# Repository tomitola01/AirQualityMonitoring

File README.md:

# Air Quality Monitoring System
This repository includes the Arduino C code (monitoring_arduinoC.ino) for the air quality monitoring system. To be used with the ESP32 microcontroller, a BME680 sensor, a push button for input, and an Adafruit 128x32 OLED. <br />
\
<br/>
\
Below shows the Adafruit display on the breadboard prototype with the system working as expected.
<br/>
\
The circuit schematics and PCB for the system can be found in the circuit_files folder. <br />
The CAD folder contains the 3D design of the monitoring system housing. Fusion 360 is needed to open the .fz3 file. <br />
\
Also included is the HTML file (monitoring_webserver.html) to build the web server with the ESP32. <br />
To build the server: 
1. Download the Monitoring_Code folder
2. Open the project using Ardunio
3. Upload the sketch to the ESP32 and run it
4. Open the serial monitor and use obtain the ESP32's IP address
5. Enter IP address into web browser

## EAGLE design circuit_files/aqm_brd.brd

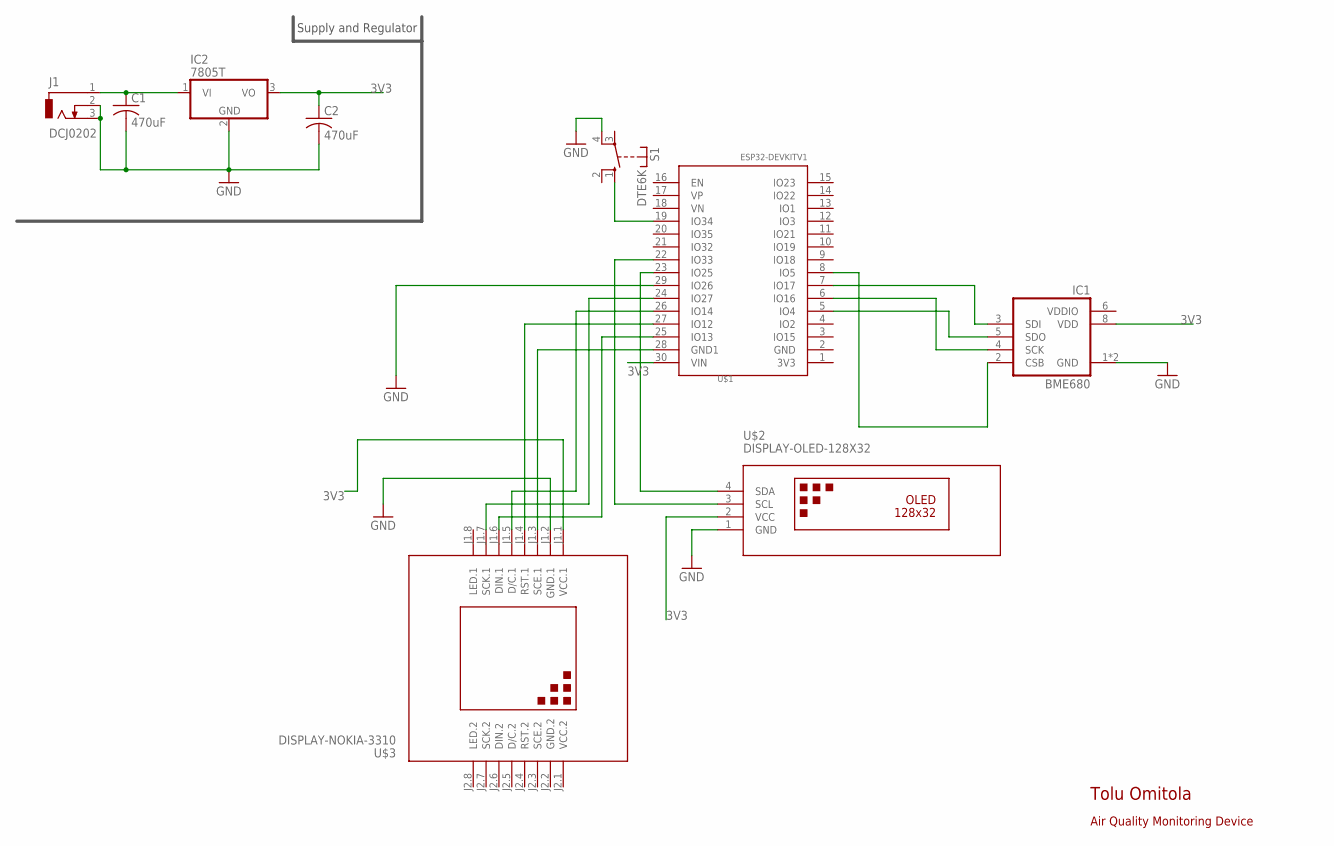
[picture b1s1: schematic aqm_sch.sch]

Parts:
C1, C2: 470uF; C075-052X106
IC1: BME680
IC2: 7805T; TO220H
J1: DCJ0202
S1: DTE6K
U$1: ESP32DEVKITV1; ESP32-DEVKITV1
U$2: DISPLAY-OLED-128X32
U$3: DISPLAY-NOKIA-3310

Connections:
3V3: C2.1, IC1.8 (VDD), IC2.3 (VO), U$1.30 (VIN), U$2.2 (VCC), U$3.J1.1 (VCC.1)
GND: C1.2, C2.2, IC1.1 (GND), IC1.7 (GND), IC2.2 (GND), J1.2, J1.3, S1.4, U$1.29 (IO26), U$2.1 (GND), U$3.J1.2 (GND.1)
GND.2: U$3.J2.2 (GND.2)
unnamed: U$1.26 (IO14), U$3.J1.5 (D/C.1)
unnamed: U$1.28 (GND1), U$3.J1.3 (SCE.1)
unnamed: U$1.24 (IO27), U$3.J1.7 (SCK.1)
unnamed: U$1.25 (IO13), U$3.J1.6 (DIN.1)
unnamed: C1.1, IC2.1 (VI), J1.1
unnamed: U$1.23 (IO25), U$2.4 (SDA)
unnamed: IC1.2 (CSB), U$1.8 (IO5)
unnamed: U$1.22 (IO33), U$2.3 (SCL)
unnamed: IC1.4 (SCK), U$1.6 (IO16)
unnamed: IC1.5 (SDO), U$1.5 (IO4)
unnamed: U$1.27 (IO12), U$3.J1.4 (RST.1)
unnamed: IC1.3 (SDI), U$1.7 (IO17)
unnamed: S1.1 (S), U$1.19 (IO34)
VCC.2: U$3.J2.1 (VCC.2)
VDDIO: IC1.6 (VDDIO)

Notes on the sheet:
Supply and Regulator
Tolu Omitola
Air Quality Monitoring Device

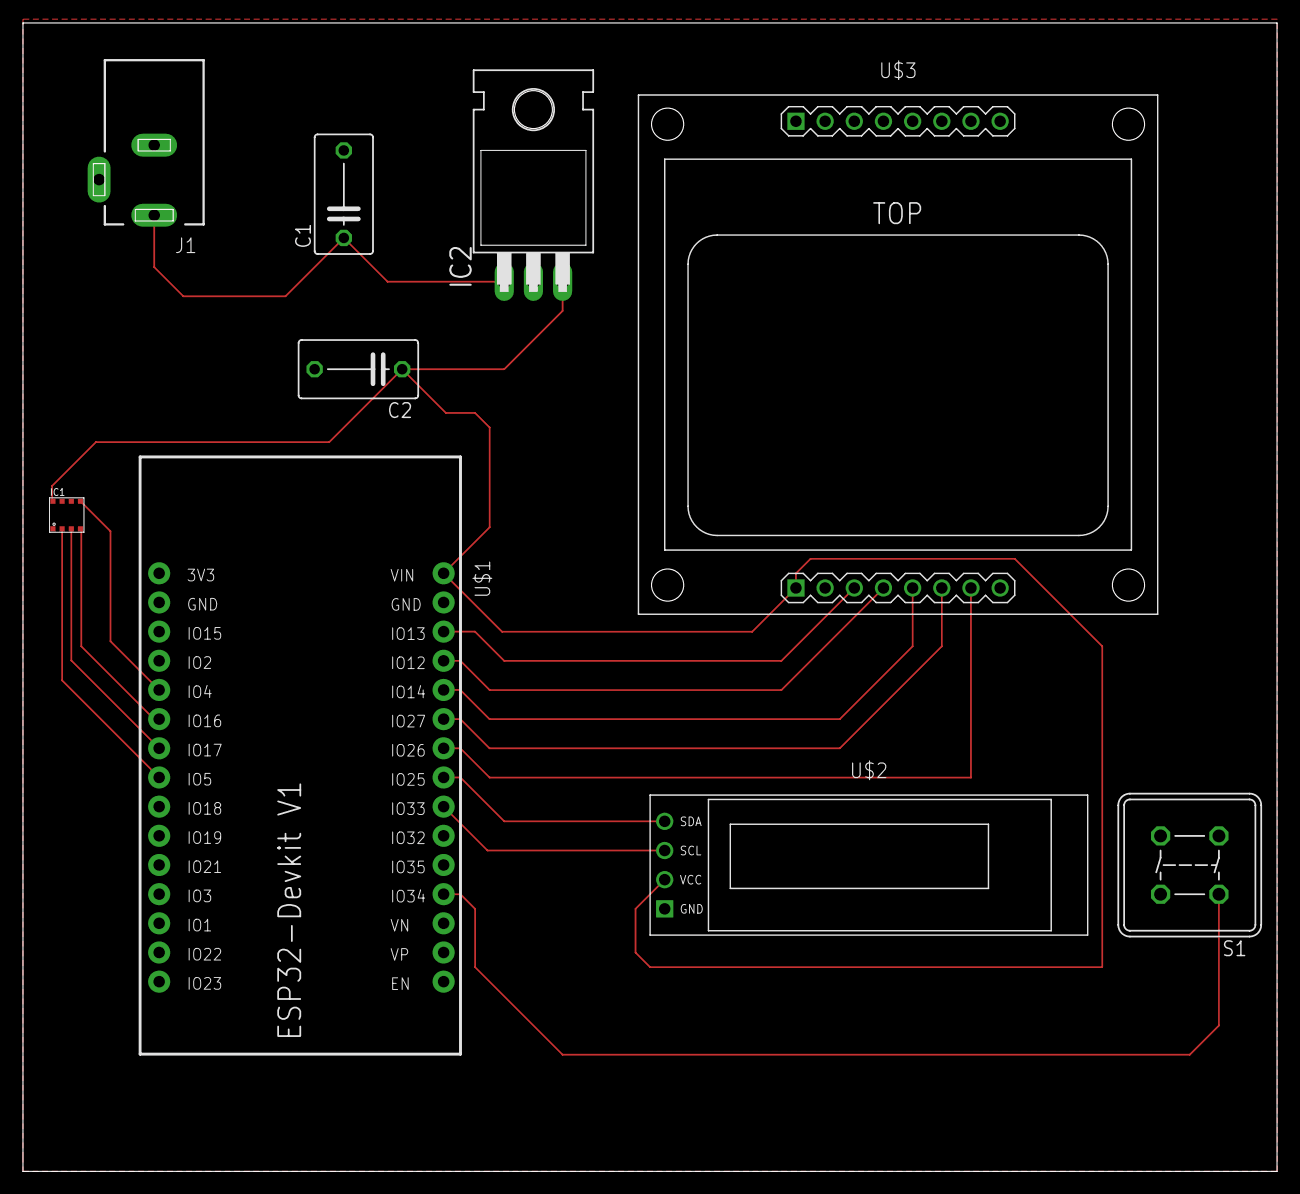
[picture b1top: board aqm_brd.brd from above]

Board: 2 copper layers, 109.2 x 100.0 mm, 9 parts (0 on the bottom side), 15 nets.

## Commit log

2021-08-13 Rename index.html to Monitoring_Webpage.html
2021-08-13 Rename bmefinal.ino to AirQualityMonitoring_ArduinoC.ino
2021-08-13 Rename AirQualityMonitoring_ArduinoC.ino to Monitoring_ArduinoC.ino
2021-08-13 Rename Monitoring_ArduinoC.ino to monitoring_arduinoC.ino
2021-08-13 Rename Monitoring_Webpage.html to monitoring_webpage.html
2021-08-13 Rename monitoring_webpage.html to monitoring_webserver.html
2023-09-07 Create place
2023-09-07 Create CAD

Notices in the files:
parts and their libraries:
diy-modules: Released under the Creative Commons Attribution 4.0 International License: http://creativecommons.org/licenses/by/4.0
